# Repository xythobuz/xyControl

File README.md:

![Logo][logo]

[xyControl][gh] is a Quadrocopter Flight Controller based on Atmels Atmega2560 microcontroller.
It features 512KB SRAM on-board, using the external memory interface of this processor.
Also included is a switched power supply as well as a USB connection to communicate with and program the target.
All I/O pins, including 3 additional UARTs, SPI, I2C (TWI) and 16 ADC Channels, are accessible via standard 2.54mm connectors.
The Board can be powered from an external stable 5V supply, USB or 7V or more, via the on-board switched power supply. All voltage sources can be selected via jumpers.

# License

Peter Fleurys TWI Library (twi.c & twi.h) is released under the GNU GPL license.

Everything else is released under a BSD-Style license. See the accompanying COPYING file.

 [gh]: http://www.xythobuz.de/xycontrol/
 [logo]: http://www.xythobuz.de/xycontrol/logo.png

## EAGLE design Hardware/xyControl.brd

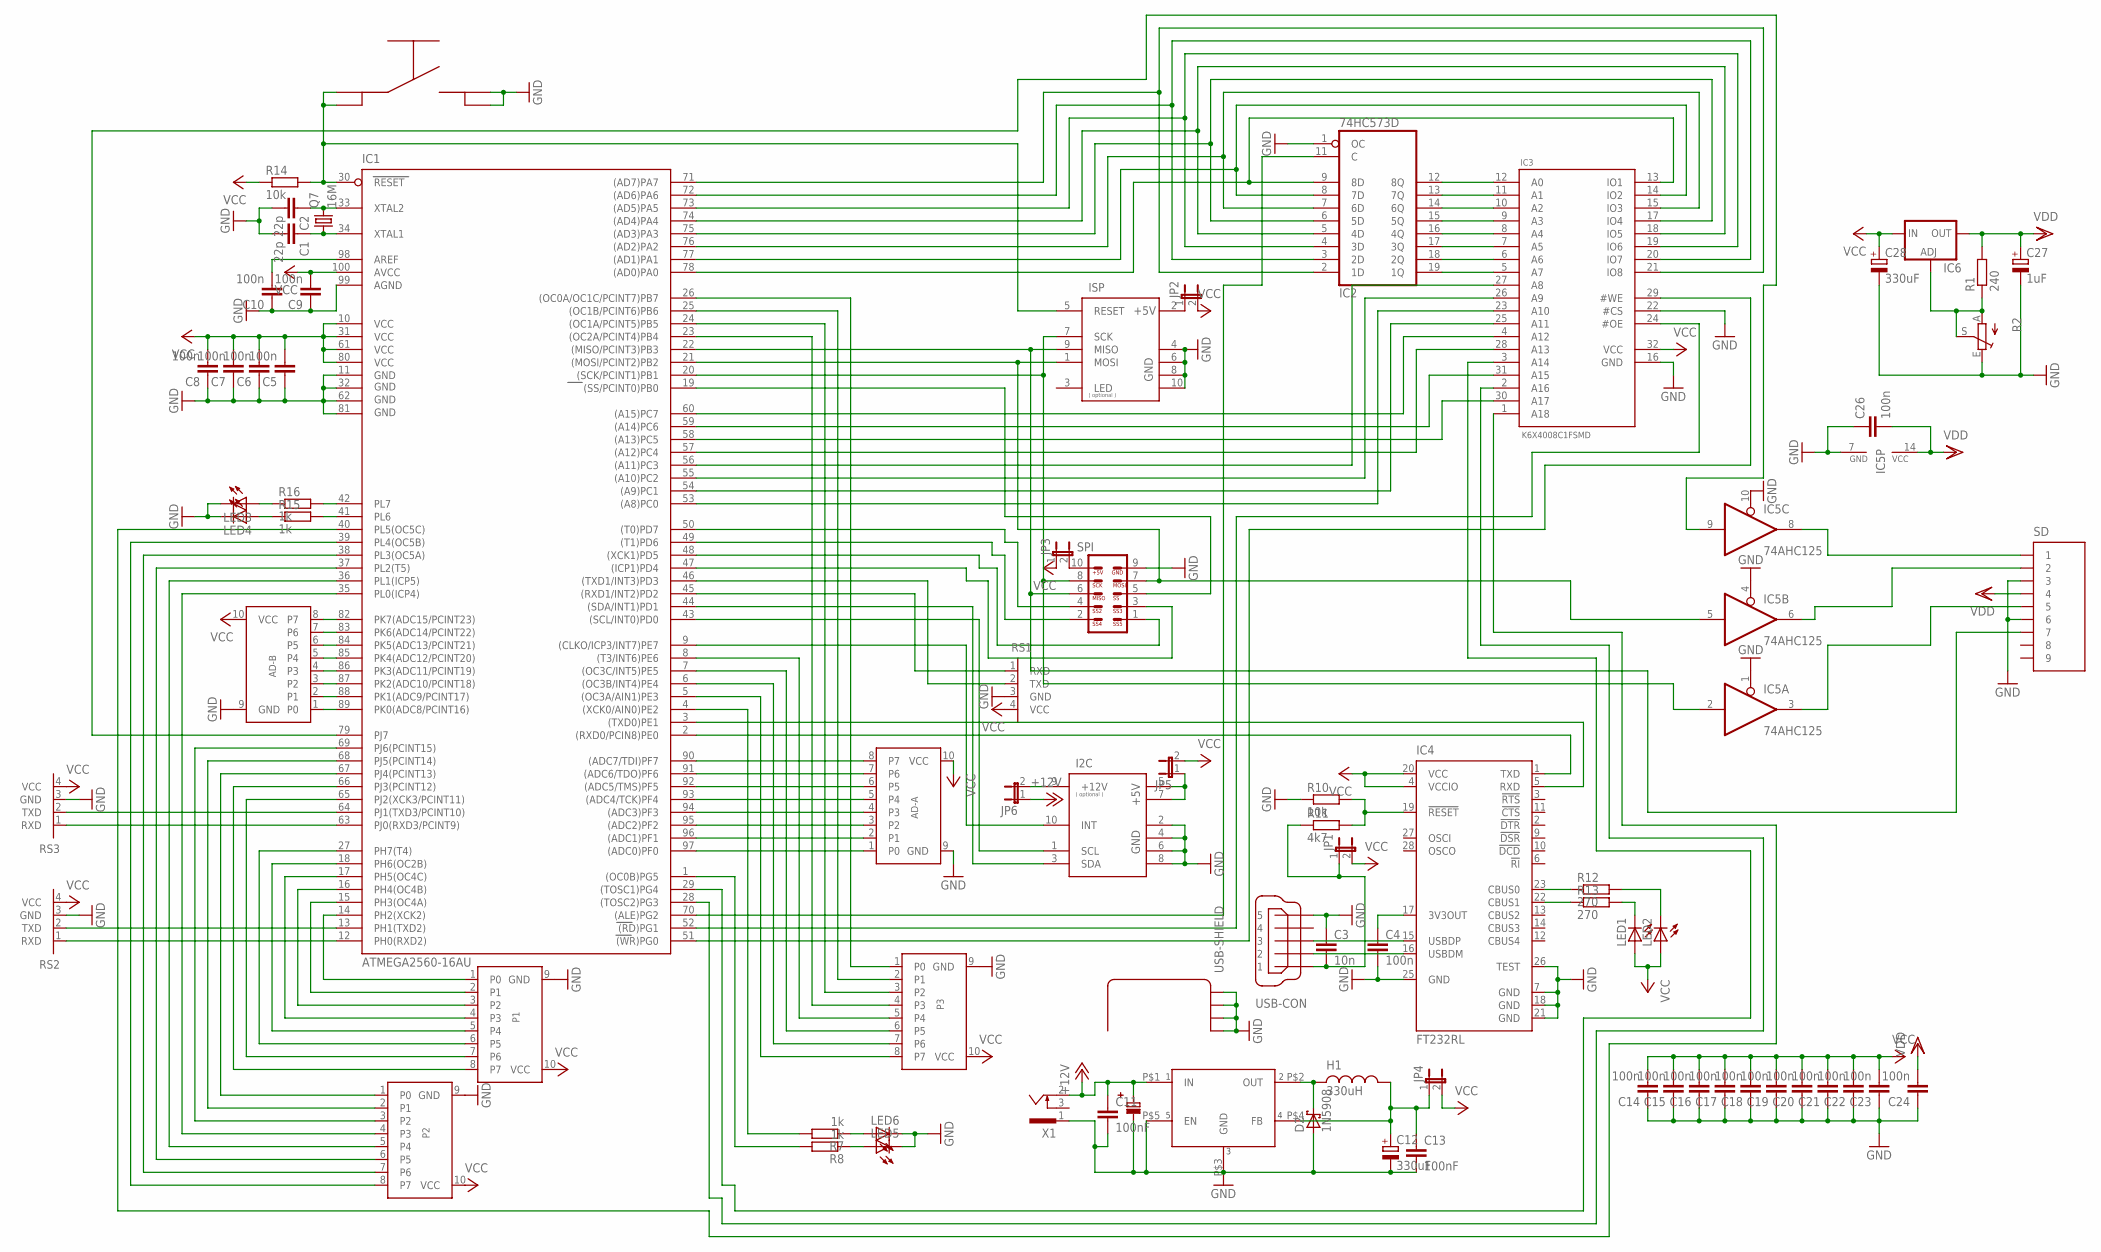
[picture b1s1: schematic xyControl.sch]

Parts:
AD-A: PORT; ML10
AD-B: PORT; ML10
C1, C2: 22p; C0603K
C3: 10n; C0603K
C4, C5, C6, C7, C8, C9, C10, C14, C15, C16, C17, C18, C19, C20, C21, C22, C23, C24, C26: 100n; C0603K
C11, C13: 100nF; C0603K
C12: 330uF; PANASONIC_F
C25: 100uF; ELKO_SMD_6.5
C27: 1uF; E2,5-6
C28: 330uF; E5-10,5
D2: 1N5908; C4111-15
H1: 330uH; PISR
I2C: I2C; ML10
IC1: ATMEGA2560-16AU; TQFP100
IC2: 74HC573D; SO20W
IC3: K6X4008C1FSMD; SOP-32
IC4: FT232RL; SSOP28
IC5: 74AHC125; SO14
IC6: LM317L; 317L
ISP: AVR-ISP; ML10
JP1, JP2, JP3, JP4, JP5, JP6: JP1E; JP1
LED1, LED2, LED3, LED4, LED5, LED6: LEDCHIP-LED0603; CHIP-LED0603
LM2576-5: LM2576; TO-220
P1, P2, P3: PORT; ML10
Q7: 16M; HC49/S
R1: 240; R0603
R2: POT_TRIM_EU-ST10; POT_ST10
R7, R8, R15, R16: 1k; R0603
R10, R14: 10k; R0603
R11: 4k7; R0603
R12, R13: 270; R0603
RS1, RS2, RS3: RS232_TTL; 1X04
SD: FPS009-30003; FPS009-3003
SPI: SPISTECKER; ML10
T1: 0-XYTHOBUZ_TASTER; 0-XYTHOBUZ_SMDTASTER
USB: 1_USER_USB-B-MINI-SMD
X1: CON-CONRAD_733980-62

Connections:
+12V: C11.1, C25.P$2, JP6.1, LM2576-5.P$1 (IN), X1.2
GND: AD-A.9 (GND), AD-B.9 (GND), C1.2, C2.2, C3.1, C4.2, C5.1, C6.1, C7.1, C8.1, C9.1, C10.1, C11.2, C12.-, C13.2, C14.1, C15.1, C16.1, C17.1, C18.1, C19.1, C20.1, C21.1, C22.1, C23.1, C24.1, C25.P$1, C26.1, C27.-, C28.-, D2.A, I2C.2 (GND), I2C.4 (GND), I2C.6 (GND), I2C.8 (GND), IC1.11 (GND), IC1.32 (GND1), IC1.62 (GND2), IC1.81 (GND3), IC1.99 (AGND), IC2.1 (OC), IC2.10 (GND), IC3.16 (GND), IC3.22 (#CS), IC4.7 (GND), IC4.18 (GND), IC4.21 (GND), IC4.25 (GND), IC4.26 (TEST), IC5.1 (OE), IC5.4 (OE), IC5.7 (GND), IC5.10 (OE), ISP.4 (GND), ISP.6 (GND), ISP.8 (GND), ISP.10 (GND), LED3.C, LED4.C, LED5.C, LED6.C, LM2576-5.P$3 (GND), LM2576-5.P$5 (EN), P1.9 (GND), P2.9 (GND), P3.9 (GND), R2.E, R10.1, RS1.3 (GND), RS2.3 (GND), RS3.3 (GND), SD.3, SD.6, SPI.9, T1.B, T1.B2, USB.5, USB.M1 (S1), USB.M2 (S2), USB.M3 (S3), USB.M4 (S4), X1.1
unnamed: IC1.78 ((AD0)PA0), IC2.9 (8D), IC3.13 (IO1)
unnamed: IC1.77 ((AD1)PA1), IC2.8 (7D), IC3.14 (IO2)
unnamed: IC1.76 ((AD2)PA2), IC2.7 (6D), IC3.15 (IO3)
unnamed: IC1.75 ((AD3)PA3), IC2.6 (5D), IC3.17 (IO4)
unnamed: IC1.74 ((AD4)PA4), IC2.5 (4D), IC3.18 (IO5)
unnamed: IC1.73 ((AD5)PA5), IC2.4 (3D), IC3.19 (IO6)
unnamed: IC1.72 ((AD6)PA6), IC2.3 (2D), IC3.20 (IO7)
unnamed: IC1.71 ((AD7)PA7), IC2.2 (1D), IC3.21 (IO8)
unnamed: IC2.12 (8Q), IC3.12 (A0)
unnamed: IC2.13 (7Q), IC3.11 (A1)
unnamed: IC2.14 (6Q), IC3.10 (A2)
unnamed: IC2.15 (5Q), IC3.9 (A3)
unnamed: IC2.16 (4Q), IC3.8 (A4)
unnamed: IC2.17 (3Q), IC3.7 (A5)
unnamed: IC2.18 (2Q), IC3.6 (A6)
unnamed: IC2.19 (1Q), IC3.5 (A7)
unnamed: IC1.2 ((RXD0/PCIN8)PE0), IC4.1 (TXD)
unnamed: IC1.3 ((TXD0)PE1), IC4.5 (RXD)
unnamed: ISP.2 (+5V), JP2.1
unnamed: JP3.2, SPI.10
unnamed: IC1.19 ((SS/PCINT0)PB0), SPI.5
unnamed: IC1.50 ((T0)PD7), SPI.4
unnamed: IC1.49 ((T1)PD6), SPI.2
unnamed: IC1.48 ((XCK1)PD5), SPI.1
unnamed: IC1.53 ((A8)PC0), IC3.23 (A10)
unnamed: IC1.54 ((A9)PC1), IC3.25 (A11)
unnamed: IC1.55 ((A10)PC2), IC3.26 (A9)
unnamed: IC1.56 ((A11)PC3), IC3.27 (A8)
unnamed: IC1.57 ((A12)PC4), IC3.28 (A13)
unnamed: IC1.58 ((A13)PC5), IC3.30 (A17)
unnamed: IC1.59 ((A14)PC6), IC3.31 (A15)
unnamed: IC1.60 ((A15)PC7), IC3.4 (A12)
unnamed: IC1.47 ((ICP1)PD4), SPI.3
unnamed: IC1.70 ((ALE)PG2), IC2.11 (C)
unnamed: IC1.52 ((RD)PG1), IC3.24 (#OE)
unnamed: IC1.51 ((WR)PG0), IC3.29 (#WE)
unnamed: IC1.20 ((SCK/PCINT1)PB1), IC5.2 (I), ISP.7 (SCK), SPI.8
unnamed: IC1.22 ((MISO/PCINT3)PB3), ISP.9 (MISO), SD.7, SPI.6
unnamed: IC1.21 ((MOSI/PCINT2)PB2), IC5.5 (I), ISP.1 (MOSI), SPI.7
unnamed: IC1.30 (RESET), ISP.5 (RESET), R14.2, T1.A, T1.A2
unnamed: I2C.5 (+5V), I2C.7 (+5V), JP5.1
unnamed: I2C.1 (SCL), IC1.43 ((SCL/INT0)PD0)
unnamed: I2C.3 (SDA), IC1.44 ((SDA/INT1)PD1)
unnamed: I2C.10 (INT), IC1.9 ((CLKO/ICP3/INT7)PE7)
unnamed: IC1.46 ((TXD1/INT3)PD3), RS1.2 (TXD)
unnamed: IC1.45 ((RXD1/INT2)PD2), RS1.1 (RXD)
unnamed: IC1.64 (PJ1(TXD3/PCINT10)), RS3.2 (TXD)
unnamed: IC1.63 (PJ0(RXD3/PCINT9)), RS3.1 (RXD)
unnamed: IC1.13 (PH1(TXD2)), RS2.2 (TXD)
unnamed: IC1.12 (PH0(RXD2)), RS2.1 (RXD)
unnamed: AD-A.8 (P7), IC1.90 ((ADC7/TDI)PF7)
unnamed: AD-A.7 (P6), IC1.91 ((ADC6/TDO)PF6)
unnamed: AD-A.6 (P5), IC1.92 ((ADC5/TMS)PF5)
unnamed: AD-A.1 (P0), IC1.97 ((ADC0)PF0)
unnamed: AD-A.2 (P1), IC1.96 ((ADC1)PF1)
unnamed: AD-A.3 (P2), IC1.95 ((ADC2)PF2)
unnamed: AD-A.4 (P3), IC1.94 ((ADC3)PF3)
unnamed: AD-A.5 (P4), IC1.93 ((ADC4/TCK)PF4)
unnamed: IC1.28 ((TOSC2)PG3), IC3.2 (A16)
unnamed: C1.1, IC1.34 (XTAL1), Q7.1
unnamed: AD-B.1 (P0), IC1.89 (PK0(ADC8/PCINT16))
unnamed: AD-B.2 (P1), IC1.88 (PK1(ADC9/PCINT17))
unnamed: AD-B.3 (P2), IC1.87 (PK2(ADC10/PCINT18))
unnamed: AD-B.4 (P3), IC1.86 (PK3(ADC11/PCINT19))
unnamed: AD-B.5 (P4), IC1.85 (PK4(ADC12/PCINT20))
unnamed: AD-B.6 (P5), IC1.84 (PK5(ADC13/PCINT21))
unnamed: AD-B.7 (P6), IC1.83 (PK6(ADC14/PCINT22))
unnamed: AD-B.8 (P7), IC1.82 (PK7(ADC15/PCINT23))
unnamed: IC1.29 ((TOSC1)PG4), IC3.3 (A14)
unnamed: LED6.A, R7.1
unnamed: LED5.A, R8.1
unnamed: IC4.16 (USBDM), USB.2
unnamed: C4.1, IC4.17 (3V3OUT)
unnamed: IC4.15 (USBDP), USB.3
unnamed: IC4.19 (!RESET), R10.2, R11.2
unnamed: IC1.79 (PJ7), IC5.9 (I)
unnamed: IC5.3 (O), SD.5
unnamed: IC5.6 (O), SD.2
unnamed: IC5.8 (O), SD.1
unnamed: IC4.23 (CBUS0), R12.1
unnamed: C3.2, JP1.1, R11.1, USB.1
unnamed: IC4.22 (CBUS1), R13.1
unnamed: IC6.1 (ADJ), R1.1, R2.A, R2.S
unnamed: LED1.C, R13.2
unnamed: LED2.C, R12.2
unnamed: C2.1, IC1.33 (XTAL2), Q7.2
unnamed: D2.C, H1.P$1, LM2576-5.P$2 (OUT)
unnamed: C12.+, C13.1, H1.P$2, JP4.1, LM2576-5.P$4 (FB)
unnamed: IC1.14 (PH2(XCK2)), P1.1 (P0)
unnamed: IC1.15 (PH3(OC4A)), P1.2 (P1)
unnamed: I2C.9 (+12V), JP6.2
unnamed: IC1.16 (PH4(OC4B)), P1.3 (P2)
unnamed: C10.2, IC1.98 (AREF)
unnamed: IC1.17 (PH5(OC4C)), P1.4 (P3)
unnamed: IC1.18 (PH6(OC2B)), P1.5 (P4)
unnamed: IC1.27 (PH7(T4)), P1.6 (P5)
unnamed: IC1.65 (PJ2(XCK3/PCINT11)), P1.7 (P6)
unnamed: IC1.66 (PJ3(PCINT12)), P1.8 (P7)
unnamed: IC1.67 (PJ4(PCINT13)), P2.1 (P0)
unnamed: IC1.68 (PJ5(PCINT14)), P2.2 (P1)
unnamed: IC1.69 (PJ6(PCINT15)), P2.3 (P2)
unnamed: IC1.35 (PL0(ICP4)), P2.4 (P3)
unnamed: IC1.36 (PL1(ICP5)), P2.5 (P4)
unnamed: IC1.37 (PL2(T5)), P2.6 (P5)
unnamed: IC1.38 (PL3(OC5A)), P2.7 (P6)
unnamed: IC1.39 (PL4(OC5B)), P2.8 (P7)
unnamed: IC1.40 (PL5(OC5C)), IC3.1 (A18)
unnamed: IC1.41 (PL6), R15.2
unnamed: IC1.42 (PL7), R16.2
unnamed: LED4.A, R15.1
unnamed: LED3.A, R16.1
unnamed: IC1.1 ((OC0B)PG5), R8.2
unnamed: IC1.4 ((XCK0/AIN0)PE2), R7.2
unnamed: IC1.5 ((OC3A/AIN1)PE3), P3.8 (P7)
unnamed: IC1.6 ((OC3B/INT4)PE4), P3.7 (P6)
unnamed: IC1.7 ((OC3C/INT5)PE5), P3.6 (P5)
unnamed: IC1.8 ((T3/INT6)PE6), P3.5 (P4)
unnamed: IC1.23 ((OC2A/PCINT4)PB4), P3.4 (P3)
unnamed: IC1.24 ((OC1A/PCINT5)PB5), P3.3 (P2)
unnamed: IC1.25 ((OC1B/PCINT6)PB6), P3.2 (P1)
unnamed: IC1.26 ((OC0A/OC1C/PCINT7)PB7), P3.1 (P0)
VCC: AD-A.10 (VCC), AD-B.10 (VCC), C5.2, C6.2, C7.2, C8.2, C9.2, C14.2, C15.2, C16.2, C17.2, C18.2, C19.2, C20.2, C21.2, C22.2, C23.2, C28.+, IC1.10 (VCC), IC1.31 (VCC1), IC1.61 (VCC2), IC1.80 (VCC3), IC1.100 (AVCC), IC2.20 (VCC), IC3.32 (VCC), IC4.4 (VCCIO), IC4.20 (VCC), IC6.3 (IN), JP1.2, JP2.2, JP3.1, JP4.2, JP5.2, LED1.A, LED2.A, P1.10 (VCC), P2.10 (VCC), P3.10 (VCC), R14.1, RS1.4 (VCC), RS2.4 (VCC), RS3.4 (VCC)
VDD: C24.2, C26.2, C27.+, IC5.14 (VCC), IC6.2 (OUT), R1.2, SD.4

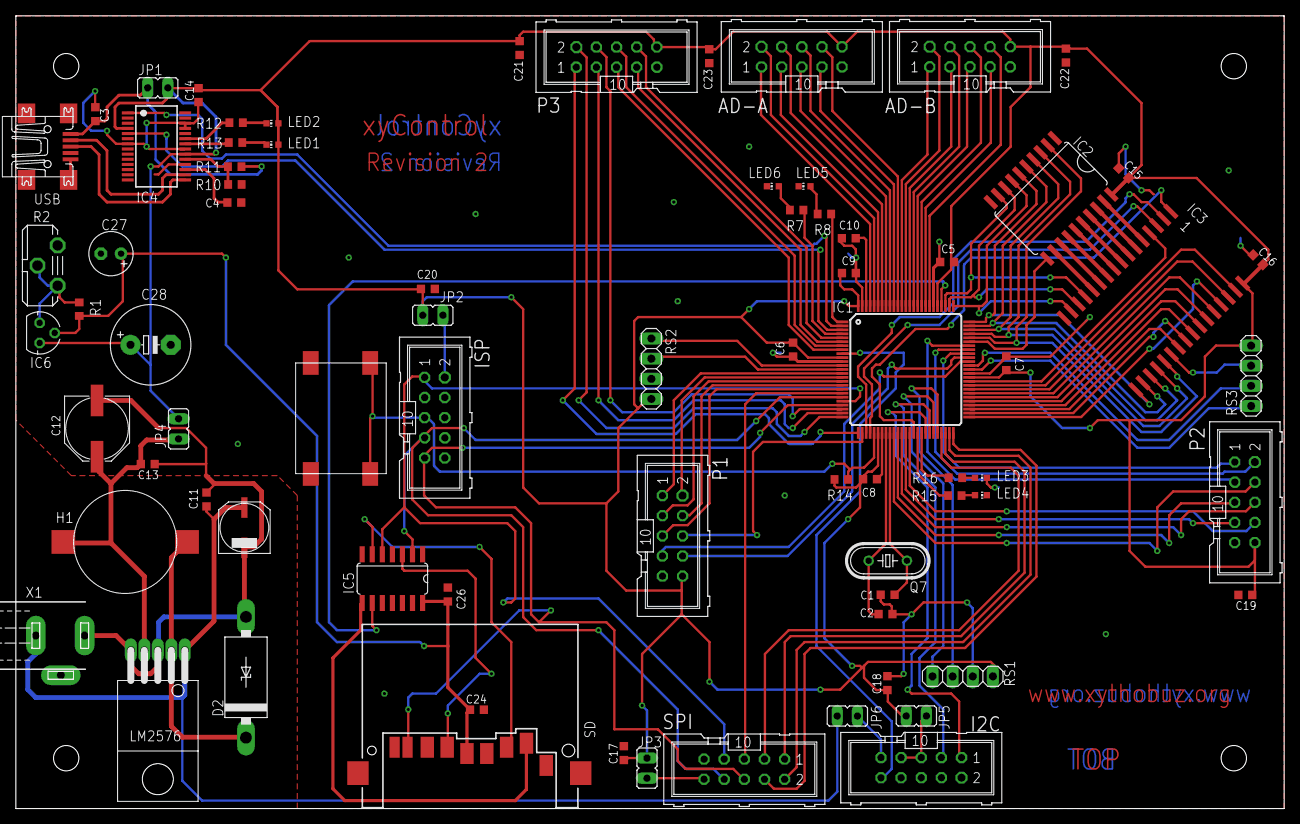
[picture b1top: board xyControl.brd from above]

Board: 2 copper layers, 160.0 x 100.0 mm, 76 parts (0 on the bottom side), 125 nets.

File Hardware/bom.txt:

Partlist

C1 + C2     22p             0603
C3          10n             0603
C4 - C11    100n            0603
C12         330u            Elko SMD
C13 - C24   100n            0603
C25         100u            Elko SMD 6.5
C26         100n            0603
C27         1u              Elko 2.5 - 6
C28         330u            Elko 5 - 10.5

LED1        -               0603
LED2        -               0603
LED3        -               0603
LED4        -               0603
LED5        -               0603
LED6        -               0603

R1          240             0603
R2          2k5             Pot ST10
R7          1k              0603
R8          1k              0603
R10         10k             0603
R11         4k7             0603
R12         270             0603
R13         270             0603
R14         10k             0603
R15         1k              0603
R16         1k              0603

IC1         ATMEGA2560      TQFP100
IC2         74HC573D        SO20W
IC3         K6X4008C1FSMD   SOP-32
IC4         FT232RL         SSOP28
IC5         74AHC125        SO14
IC6         LM317L          TO-92
IC7         LM2576          TO-220

D2          1N5908          C4111-15
H1          330uH           PISR
Q7          16M             HC49/S

JP1         -               Jumper 1x2
JP2         -               Jumper 1x2
JP3         -               Jumper 1x2
JP4         -               Jumper 1x2
JP5         -               Jumper 1x2
JP6         -               Jumper 1x2
RS1         -               Jumper 1x4
RS2         -               Jumper 1x4
RS3         -               Jumper 1x4

SPI         -               ML10
I2C         -               ML10
AD-A        -               ML10
AD-B        -               ML10
P1          -               ML10
P2          -               ML10
P3          -               ML10
ISP         -               ML10

T1          -               SMD Button

USB         USB-B Mini      SMD
SD          -               FPS009-30003

X1          -               Conrad 733980-62

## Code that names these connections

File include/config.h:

/*
 * config.h
 *
 * Copyright (c) 2013, Thomas Buck <xythobuz@me.com>
 * All rights reserved.
 *
 * Redistribution and use in source and binary forms, with or without
 * modification, are permitted provided that the following conditions
 * are met:
 *
 * - Redistributions of source code must retain the above copyright notice,
 *   this list of conditions and the following disclaimer.
 *
 * - Redistributions in binary form must reproduce the above copyright
 *   notice, this list of conditions and the following disclaimer in the
 *   documentation and/or other materials provided with the distribution.
 *
 * THIS SOFTWARE IS PROVIDED BY THE COPYRIGHT HOLDERS AND CONTRIBUTORS
 * "AS IS" AND ANY EXPRESS OR IMPLIED WARRANTIES, INCLUDING, BUT NOT LIMITED
 * TO, THE IMPLIED WARRANTIES OF MERCHANTABILITY AND FITNESS FOR A PARTICULAR
 * PURPOSE ARE DISCLAIMED. IN NO EVENT SHALL THE COPYRIGHT HOLDER OR
 * CONTRIBUTORS BE LIABLE FOR ANY DIRECT, INDIRECT, INCIDENTAL, SPECIAL,
 * EXEMPLARY, OR CONSEQUENTIAL DAMAGES (INCLUDING, BUT NOT LIMITED TO,
 * PROCUREMENT OF SUBSTITUTE GOODS OR SERVICES; LOSS OF USE, DATA, OR
 * PROFITS; OR BUSINESS INTERRUPTION) HOWEVER CAUSED AND ON ANY THEORY OF
 * LIABILITY, WHETHER IN CONTRACT, STRICT LIABILITY, OR TORT (INCLUDING
 * NEGLIGENCE OR OTHERWISE) ARISING IN ANY WAY OUT OF THE USE OF THIS
 * SOFTWARE, EVEN IF ADVISED OF THE POSSIBILITY OF SUCH DAMAGE.
 */
#ifndef _config_h
#define _config_h

/** \addtogroup config Configuration
 *  Various default settings.
 *  @{
 */

 /** \file config.h
 *  Various default settings.
 */

//  -----------------
// |    Filtering    |
//  -----------------

#define FILTER_KALMAN 0
#define FILTER_COMPLEMENTARY 1
#define ORIENTATION_FILTER FILTER_KALMAN /**< Filter Implementation to be used */

/** Time Contant for Low and High Pass Filter in the Complementary Filter.
 *  In essence, time periods shorter than TAU come from gyro data,
 *  longer time periods come from the Accelerometer data.
 *  In seconds!
 */
#define COMPLEMENTARY_TAU 0.5

// 1 has no effect, bigger numbers dampen the signal more
#define SOFTWARELOWPASS 1 /**< Software Low-Pass on Gyro and ACC */
#define ACCFILTERFACTOR SOFTWARELOWPASS /**< Accelerometer Low Pass Factor */
#define GYROFILTERFACTOR SOFTWARELOWPASS /**< Gyroscope Low Pass Factor */

#define PID_OUTMAX 256 /**< Maximum PID Output */
#define PID_OUTMIN -256 /**< Minimum PID Output */
#define PID_INTMAX PID_OUTMAX /**< Maximum PID Integral Sum */
#define PID_INTMIN PID_OUTMIN /**< Minimal PID Integral Sum */

//  -----------------
// |    Kalman      |
//  -----------------

/** Time Constant */
#define DT 0.01f // 100Hz

// Q (3x3 Matrix) with these elements on diagonal
#define Q1 5.0f /**< Q Matrix Diagonal Element 1 */
#define Q2 100.0f /**< Q Matrix Diagonal Element 2 */
#define Q3 0.01f /**< Q Matrix Diagonal Element 3 */

// R (2x2 Matrix) with these elements on diagonal
#define R1 1000.0f /**< R Matrix Diagonal Element 1 */
#define R2 1000.0f /**< R Matrix Diagonal Element 2 */

//  -----------------
// |       Set       |
//  -----------------

#define SET_ROLLPLUS 1 /**< Second Motor at the Right */
#define SET_ROLLMINUS 3 /**< Fourth Motor at the Left */
#define SET_PITCHPLUS 0 /**< First Motor at the Top */
#define SET_PITCHMINUS 2 /**< Third Motor at the Bottom */

//  -----------------
// |       PID       |
//  -----------------

#define PID_P 5.0 /**< Default PID P Constant */
#define PID_I 0.03 /**< Default PID I Constant */
#define PID_D -13.0 /**< Default PID D Constant */

//  -----------------
// |      Motor      |
//  -----------------

#define MOTORCOUNT 4  /**< Amount of motors */

//  -----------------
// |       ADC       |
//  -----------------

#define BATT_MAX 15 /**< Battery Voltage Reference (ADC 5V) */
#define BATT_CHANNEL 0 /**< ADC Channel for Battery */

//  -----------------
// |       TWI       |
//  -----------------

#define ACC_ADDRESS 0x32 /**< Accelerometer Address (0011001r) */
#define GYRO_ADDRESS 0xD6 /**< Gyroscope Address (110101xr, x = 1) */
#define MAG_ADDRESS 0x3C /**< Magnetometer Address */
#define MOTOR_BASEADDRESS 0x52 /**< Address of first motor controller */

//  -----------------
// |    xyControl    |
//  -----------------

#define LED0PORT PORTL /**< First LED Port */
#define LED0DDR DDRL /**< First LED Data Direction Register */
#define LED0PIN PL6 /**< First LED Pin */
#define LED1PORT PORTL /**< Second LED Port */
#define LED1DDR DDRL /**< Second LED Data Direction Register */
#define LED1PIN PL7 /**< Second LED Pin */
#define LED2PORT PORTG /**< Third LED Port */
#define LED2DDR DDRG /**< Third LED Data Direction Register */
#define LED2PIN PG5 /**< Third LED Pin */
#define LED3PORT PORTE /**< Fourth LED Port */
#define LED3DDR DDRE /**< Fourth LED Data Direction Register */
#define LED3PIN PE2 /**< Fourth LED Pin */

//  -----------------
// |      XMEM       |
//  -----------------

#define BANK0PORT PORTG /**< First Bank Selection Port */
#define BANK0DDR DDRG   /**< First Bank Selection Data Direction Register */
#define BANK0PIN PG3    /**< First Bank Selection Pin */
#define BANK1PORT PORTG /**< Second Bank Selection Port */
#define BANK1DDR DDRG   /**< Second Bank Selection Data Direction Register */
#define BANK1PIN PG4    /**< Second Bank Selection Pin */
#define BANK2PORT PORTL /**< Third Bank Selection Port */
#define BANK2DDR DDRL   /**< Third Bank Selection Data Direction Register */
#define BANK2PIN PL5    /**< Third Bank Selection Pin */

//  -----------------
// |       SPI       |
//  -----------------

#define SPIDDR DDRB /** SPI Data Direction Register */
#define SPIMOSI PB2 /** SPI MOSI Pin */
#define SPISCK PB1 /** SPI SCK Pin */
#define SPISS PB0 /**< SPI Slave Select Pin */

//  -----------------
// |     Serial      |
//  -----------------

#define RX_BUFFER_SIZE 64 /**< UART Receive Buffer Size */
#define TX_BUFFER_SIZE 64 /**< UART Transmit Buffer Size */

#endif
/** @} */

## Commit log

2012-11-12 Added bank switching.
2012-11-15 New 3V3 Regulator.
2012-11-15 Minor fixes.
2012-11-17 Extended XMEM bank switching.
2012-11-19 Added config file.
    Also finished first Hardware Revision!
2012-11-24 Started SD Implementation.
2012-11-25 Finished SD/MMC Driver.
2012-12-20 Added avrNetStack Task Scheduler.
2012-12-20 Task Manager is properly bank-switching.
2012-12-21 External Memory Test added.
2012-12-22 Added Servo Test.
2012-12-30 Started with servo lib.
2013-01-01 Finished servos.c library
2013-01-02 Added TWI and Gyro Libraries.
2013-01-02 Started ncurses visualizer.
2013-01-02 Extended visualizer.
2013-01-03 Added Accelerometer library.
2013-01-04 Added UART Test.
2013-01-04 Added Accelerometer Test.
2013-01-04 Added Gyroscope Test.
2013-01-05 Finished Visualizer.
2013-01-05 Added Java Tool.
2013-01-05 Extended FlightRemote
2013-01-05 Added log window.
2013-01-05 Java FlightRemote displays Accelerometer data!
2013-01-05 Fixed Gyroscope Code.
2013-01-05 Accelerometer Test calculates pitch and roll.
2013-01-05 Gyro Test calculates X rotation angle.
2013-01-05 Combined Accelerometer and Gyroscope Data.
    Using a simple Complimentary Filter.
2013-01-06 Prettier Orientation Test
2013-01-06 Added Magnetometer Library and Test.
2013-01-08 Added BL-Ctrl Test.
2013-01-11 Nicer Makefile Constants
2013-01-12 Added Low level motor library.
    Removed NCurses visualizer. Renamed Java Visualizer. Began with Java
    Telemetry App.
2013-01-12 Fixed Motorlib Test.
2013-01-12 Finished Test Motorlevel
2013-01-14 Added ADC Code.
2013-01-16 Fixed ADC.
2013-01-16 Added serial menu for human interaction.
2013-01-26 Extended Telemetry Tool. UART Menu Help sorted.
2013-01-26 UART Menu command now unsigned.
2013-01-28 Examples use Task Handler.
    Old examples moved into "old" folder, may will be made task based.
    Library registers stdin, stdout and stderr. More xyLed functionality,
    debug mode for accelerometer driver.
2013-02-11 Added Orientation Library.
2013-02-11 Ported RAM Test. Fixed standard stream memory location.
2013-02-11 Removed old tests.
2013-02-11 Added Motor Test.
2013-02-12 Added system-wide error handling.
2013-02-14 Removed Motorlevel Test.
    Extended HardwareTest. Fixed stdout, now sending CR.
2013-02-15 Can select UART module at compile time.
2013-02-15 Added Bluetooth Test.
    Can register handler for unhandled UART menu commands.
2013-02-15 Added PID Control.
2013-02-15 Extended UART Flight Firmware.
2013-02-23 Added xyCopter Android App.
2013-02-23 First working xyCopter App.
2013-02-24 Extended xyCopter App.
2013-02-24 First xyCopter App Release.
2013-02-25 Added xyCopter Screenshot in Readme.
2013-02-27 Self-Signed APK
2013-02-28 Threads in extra files.
2013-02-28 Removed Menu. Dark Theme.
2013-03-01 New Button Layout in xyCopter. Can now rotate.
2013-03-01 Fixed App Layout.
2013-03-01 Removed Visualizer. Extended tool readme.
2013-03-02 Init sequence for all libraries.
2013-03-02 Increased accelerometer range.
2013-03-02 Normalizing Gyro and ACC in their libraries.
2013-03-03 Multiple changes.
    Combined control library into pid library. All Quadrocopter Controlling
    Libraries no longer have tasks, the task is implemented in UARTFlight.
    The examples folder was removed. UARTFlight is now sending constant
    status updates. Updated xyCopter App to receive and display these
    status updates.
2013-03-03 Added License Boilerplate to xyCopter Code.
    Also fixed indentation.
2013-03-05 Added GraphView Library.
2013-03-05 Added Connect and Disconnect Buttons.
2013-03-05 Updated APK.
2013-03-05 Added Software Low-Pass Filter.
2013-03-06 xyCopter displays PID Output
2013-03-06 Now using Kalman Filter.
2013-03-06 Refactored Kalman Library.
2013-03-06 Orientation library with error reporting.
2013-03-06 Can toggle PID.
2013-03-06 xyCopter beauty fixes.
2013-03-09 Can change PID Parameters live.
2013-03-10 Dropbox support for xyCopter.
    Started implementing rudimentary firmware uploader.
2013-03-10 Added generated files again.
2013-03-10 Dropbox and YASAB for xyCopter
2013-03-11 Zeroing orientation.
2013-03-11 Added own xyCopter Logo.
2013-03-12 Tweaked control code.
2013-03-13 xyCopter prints voltage in color.
2013-03-15 Bigger GraphView with more data!
2013-03-17 Can change range live
2013-03-17 Zero angles manually
2013-03-18 Bugfix: ZeroOrientation works more than once.
2013-03-18 Faster Status Task
2013-03-21 More warnings.
2013-03-23 Added paths to makefile binaries.
2013-03-24 Added Doxyfile
2013-03-24 Started doxygen documentation.
2013-03-24 More doxygen documentation.
2013-03-25 Even more doxygen comments.
2013-03-25 Finished Doxygen Documentation.
2013-04-02 Ready to publish docs with git
2013-04-14 Can switch between kalman or complementary filter
2013-04-19 Fixed Readme
2013-04-24 Fixed PCB Layout
    SD slot is now rotated correct
2013-04-28 Included new avrSerial Library
2013-04-28 Telemetry App has basic functionality
2013-04-29 Added HardwareTest.
    UART Flight can be silenced. Tries to calculate Yaw angle. Telemetry
    displays Yaw Angle. Mag normalizes output (bug?).
2013-04-29 rebuilt docs
2013-05-06 Extended Readme
2013-05-23 xyCopter Bugfix: D-Param Cache
2013-05-23 Self-Reset if sensor data is garbage. Some refactoring of function and variable names.
2013-05-24 PID influence now absolute
2013-05-24 Added map function
2013-05-24 Renamed Global PID Vars. Set Task using 8bit Integer for diff.
2013-05-29 Fixed xyCopter Bug. Bluetooth device selection was broken.
2013-05-31 Graph Angle Speeds
2013-06-01 xyCopter builds again
2013-06-01 Can suspend output from within xyCopter
2013-06-18 Deleted Test
2013-06-26 Started new
2013-06-26 Added Error.h
2013-06-26 Added error.c
2013-06-26 It builds!
2013-06-26 Init sequence
2013-06-27 Added Remote Library
2013-07-07 Serial library using dynamic memory for buffers
2013-07-07 Rebuilt docs. Removed tools. Fixed Readme.
2013-07-09 Added UART LCD lib
2014-09-01 Fix for Atmega 1281/2561
